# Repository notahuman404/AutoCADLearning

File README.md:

# Starbie

Starbie is a small motion-controlled digital pet built around a Seeed Studio XIAO ESP32-C3. It draws a one-bit pet on a 128×64 OLED, uses an MPU6050 to read tilt and shaking, and offers a four-way action menu. A DHT11 can provide temperature and humidity readings.

## Project images

<table>
  <tr>
    <td align="center"><strong>Concept render</strong><br></td>
    <td align="center"><strong>3D PCB render</strong><br></td>
  </tr>
  <tr>
    <td align="center"><strong>PCB layout</strong><br></td>
    <td align="center"><strong>Schematic</strong><br></td>
  </tr>
</table>

## Features

- Animated pet with nap, play, feed, and pet actions.
- Tilt-controlled radial menu, using the MPU6050 as a simple air mouse.
- Shake reaction that wakes Starbie and changes its stats.
- Stats screen for joy, energy, fullness, and available sensor readings.
- Joy, energy, and fullness are saved using the ESP32 Preferences storage; stats do not drain while idle.

## Hardware

| Part | Role |
| --- | --- |
| Seeed Studio XIAO ESP32-C3 | Controller and firmware target |
| 0.96-inch 128×64 I²C OLED, SSD1306-compatible | Pet display |
| MPU6050 module (external via J2) | Tilt and shake sensing |
| DHT11 | Optional temperature and humidity sensing |
| 2 Cherry MX-compatible 1U switches | Menu/action and stats controls |
| 10 kΩ through-hole resistor | Listed as R1 in the schematic |
| Custom PCB | KiCad design in the starbie directory |

See BOM.csv for the current parts list. The guide pairs the XIAO ESP32-C3 symbol with the custom footprint ID `Imported Parts:XIAO-ESP32-C6-DIP`; the BOM preserves that assignment. The guide represents the MPU6050 module with a generic 1x08 connector: J2 is the board-mounted header and pins 1-4 carry +3.3V, GND, SCL, and SDA. The guide does not specify a particular breakout-board variant, so the BOM names it as an MPU6050 module connected via J2.

## Wiring

The firmware pin assignments are in Firmware/Starbie/Starbie.ino. OLED and MPU6050 share I²C.

| Device | XIAO connection | Notes |
| --- | --- | --- |
| OLED SDA | D4 / GPIO6 | I²C address defaults to 0x3C |
| OLED SCL | D5 / GPIO7 | Shared I²C bus |
| MPU6050 SDA | D4 / GPIO6 | I²C address defaults to 0x68 |
| MPU6050 SCL | D5 / GPIO7 | Shared I²C bus |
| DHT11 data | D1 / GPIO3 | Optional; set USE_DHT11 to false if not fitted |
| Button 1 | D2 / GPIO4 | Opens the menu; confirms the selected action |
| Button 2 | D3 / GPIO5 | Shows or hides the stats screen |

Connect module power and ground according to the module labels and the schematic. Verify voltage and pin order before powering the board.

## Firmware setup

1. Install Arduino IDE and add the Espressif ESP32 board package URL: https://espressif.github.io/arduino-esp32/package_esp32_index.json
2. Install the ESP32 board package by Espressif Systems and select XIAO_ESP32C3 under Tools → Board → esp32.
3. Install Adafruit GFX Library, Adafruit SSD1306, Adafruit MPU6050, and DHT sensor library. Accept the IDE's dependency prompts.
4. Open Firmware/Starbie/Starbie.ino, check the beginner settings and pin assignments, then upload to the XIAO ESP32-C3.

Button 1 opens the four-way menu. Tilt toward top for NAP, right for PLAY, bottom for FEED, or left for PET; press Button 1 again to confirm. Button 2 toggles stats. Shaking Starbie gives it a reaction and wakes it from a nap. The DHT11 can be disabled with USE_DHT11 if that sensor is not installed.

## Repository layout

- Firmware/Starbie/Starbie.ino — Arduino firmware.
- starbie/ — KiCad schematic, board, and project files.
- assests/ — project renders, schematic, and PCB images (the directory name is intentionally kept as it exists in the repository).
- 3D Models/ — STEP models for the display, switches, sensor module, and controller.
- Imported Parts.pretty/ — custom KiCad footprints.

## Reference

This project follows the [Starbie Week 1 guide](https://github.com/SharKingStudios/Starbie/blob/main/Week%201%20Guide.md).

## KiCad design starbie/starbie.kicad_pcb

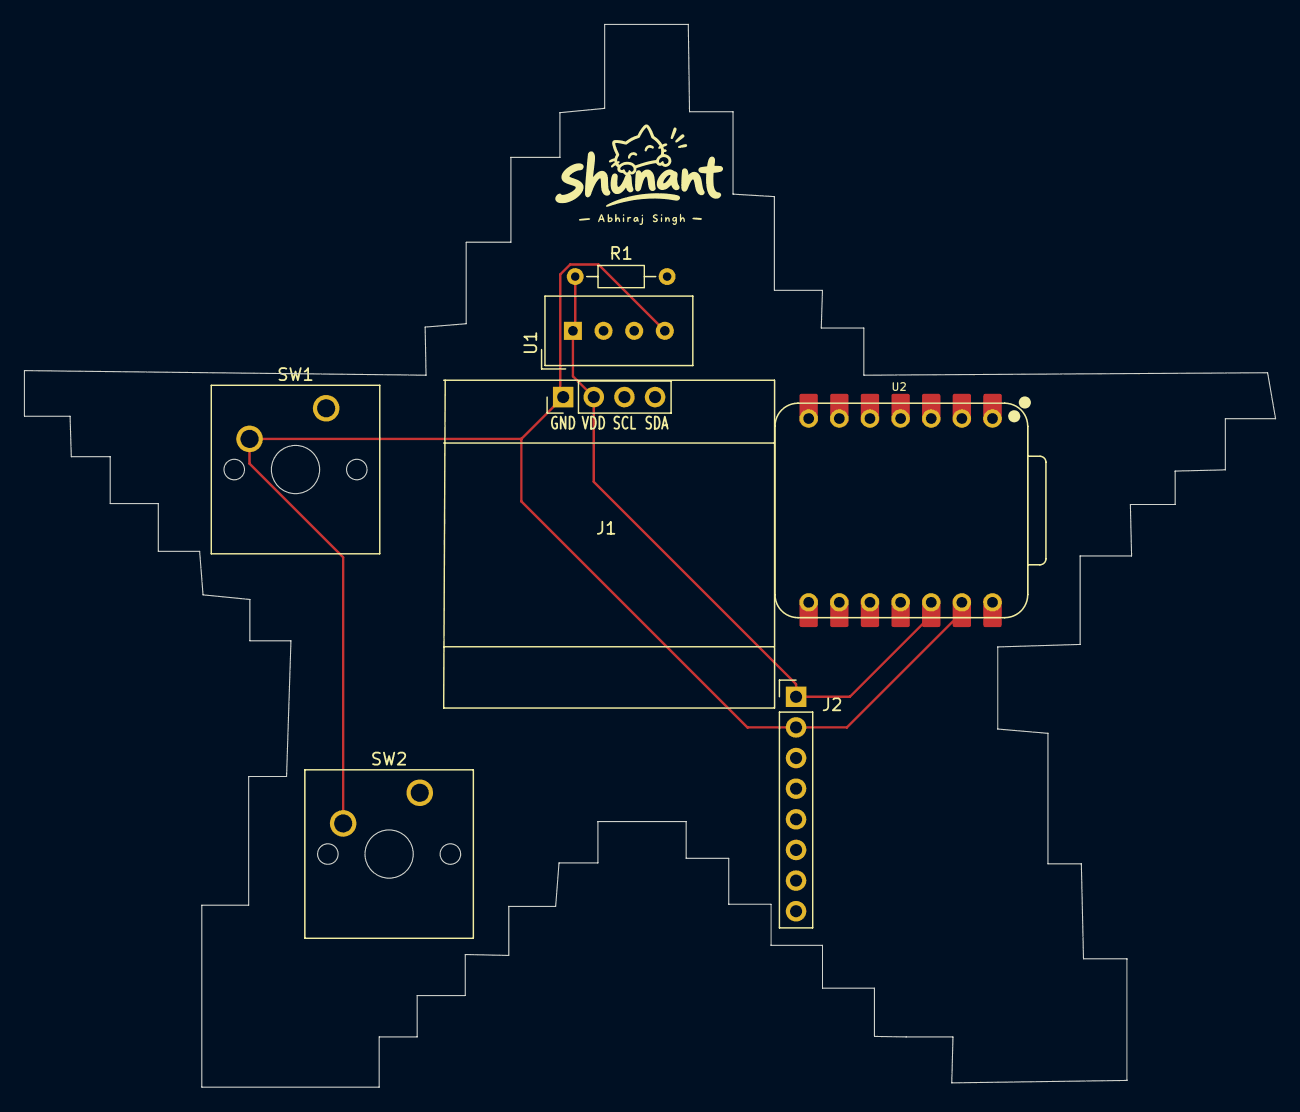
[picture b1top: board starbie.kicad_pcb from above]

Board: 2 copper layers, 103.7 x 88.1 mm, 7 parts (0 on the bottom side), 2 nets.

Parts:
J1: Conn_01x04_Pin; Display_128x64_096_I2C
J2: Conn_01x08_Pin; PinHeader_1x08_P2.54mm_Vertical
R1: 10k; R_Axial_DIN0204_L3.6mm_D1.6mm_P7.62mm_Horizontal
SW1, SW2: SW_Push; SW_Cherry_MX_1.00u_PCB
U1: DHT11; Aosong_DHT11_5.5x12.0_P2.54mm
U2: XIAO-ESP32-C3-SMD; XIAO-ESP32-C6-DIP

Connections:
+3.3V: J1.2, J2.1, R1.1, U1.1 (VDD), U2.12 (3V3_OUT)
GND: J1.1, J2.2, SW1.2 (2_2), SW2.2 (2_2), U1.4 (GND), U2.13 (GND)
